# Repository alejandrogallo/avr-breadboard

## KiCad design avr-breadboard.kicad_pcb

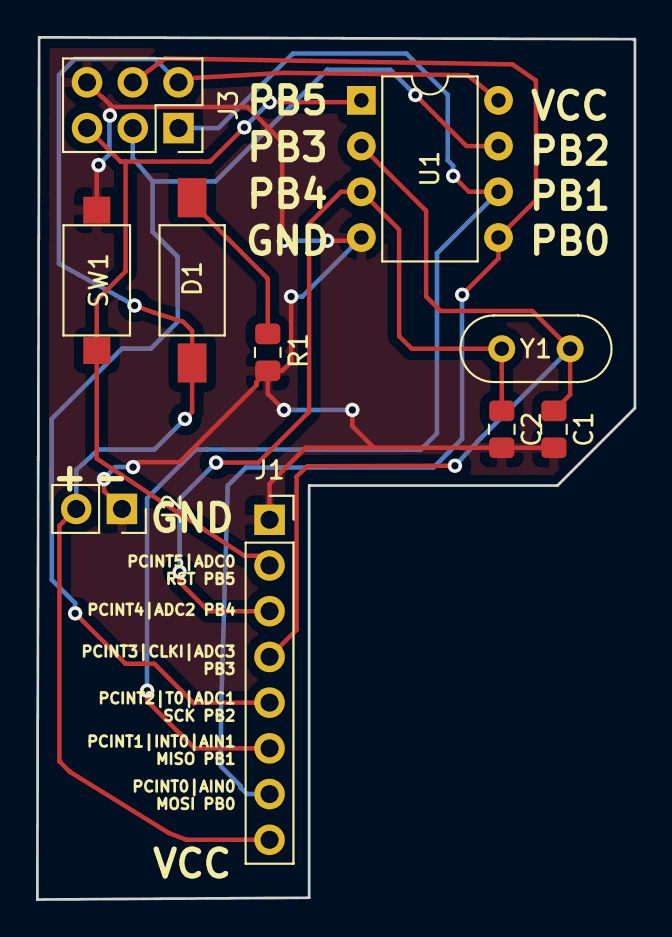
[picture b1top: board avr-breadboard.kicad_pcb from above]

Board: 2 copper layers, 33.2 x 47.9 mm, 10 parts (0 on the bottom side), 9 nets.

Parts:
C1, C2: C; C_0805_2012Metric_Pad1.15x1.40mm_HandSolder
D1: LED; SW_SPST_FSMSM
J1: Conn_01x08; PinSocket_1x08_P2.54mm_Vertical
J2: Conn_01x02; PinSocket_1x02_P2.54mm_Vertical
J3: Conn_02x03_Counter_Clockwise; PinSocket_2x03_P2.54mm_Vertical
R1: R; R_0805_2012Metric_Pad1.15x1.40mm_HandSolder
SW1: SW_Push; SW_SPST_CK_RS282G05A3
U1: ATtiny13-20PU; DIP-8_W7.62mm
Y1: Crystal; Crystal_HC52-6mm_Vertical

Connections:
GND: C1.2, C2.2, J1.1, J2.1, J3.6, R1.2, SW1.2, U1.4
MISO: J1.6, J3.1, U1.6
MOSI: J1.7, J3.4, U1.5
unnamed: D1.1, R1.1
PB3: C1.1, J1.4, U1.2, Y1.1
PB4: C2.1, J1.3, U1.3, Y1.2
RESET: J1.2, J3.5, SW1.1, U1.1
SCK: J1.5, J3.3, U1.7
VCC: D1.2, J1.8, J2.2, J3.2, U1.8

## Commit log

2019-09-17 Jlcpcbversion
